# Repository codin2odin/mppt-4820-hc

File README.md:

# MPPT charge controller with HS load switch and CAN

 Development ongoing.

Schematic: [PDF file](build/mppt-4820-hc_schematic.pdf)

Bill of Materials: [CSV file](build/mppt-4820-hc_bom(hv_supply,can).csv)

Firmware repository: [charge-controller-firmware](https://github.com/codin2odin/charge-controller-firmware)

This charge controller design is modified version of [mppt-2420-hc](https://github.com/LibreSolar/mppt-2420-hc) with goal of adding support for 36v & 48v battery systems.

## Features

- Solar input terminal
    - Max. 85V (100V MOSFETs used)
    - DC/DC converter inductor current max. 20A
- Battery output terminal
    - 10 V - 60 V (supporting 12v & 24v & 36v & 48v battery systems)
    - Max. current: 20A (limited by inductor current)
- Load terminal: 20A
- New STM32G431 ARM MCU with advanced digital power conversion features
- Expandable via Olimex Universal Extension Connector (UEXT)
- Two bi-color (red/green) LEDs for status indication. Additional user interface can be included in separate PCB in front panel housing and connected via UEXT
- CAN interface via RJ45 connectors

## Mechanical design

- TO-220 MOSFETs can be screwed to large heat sink at the back

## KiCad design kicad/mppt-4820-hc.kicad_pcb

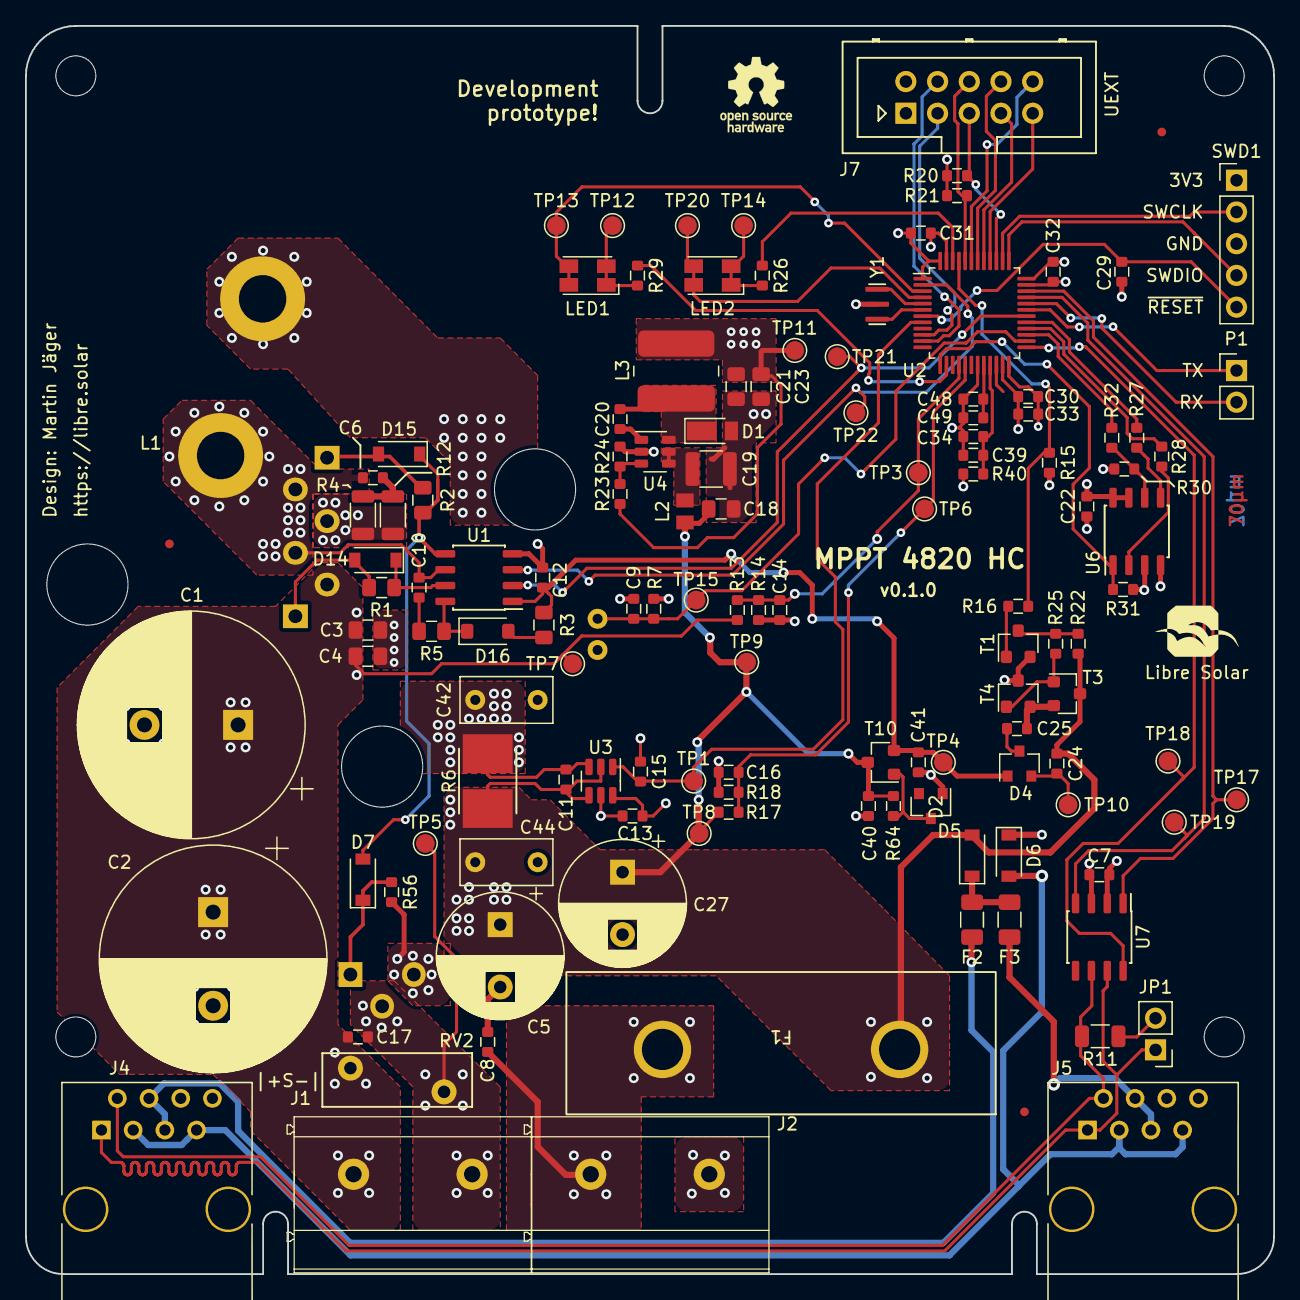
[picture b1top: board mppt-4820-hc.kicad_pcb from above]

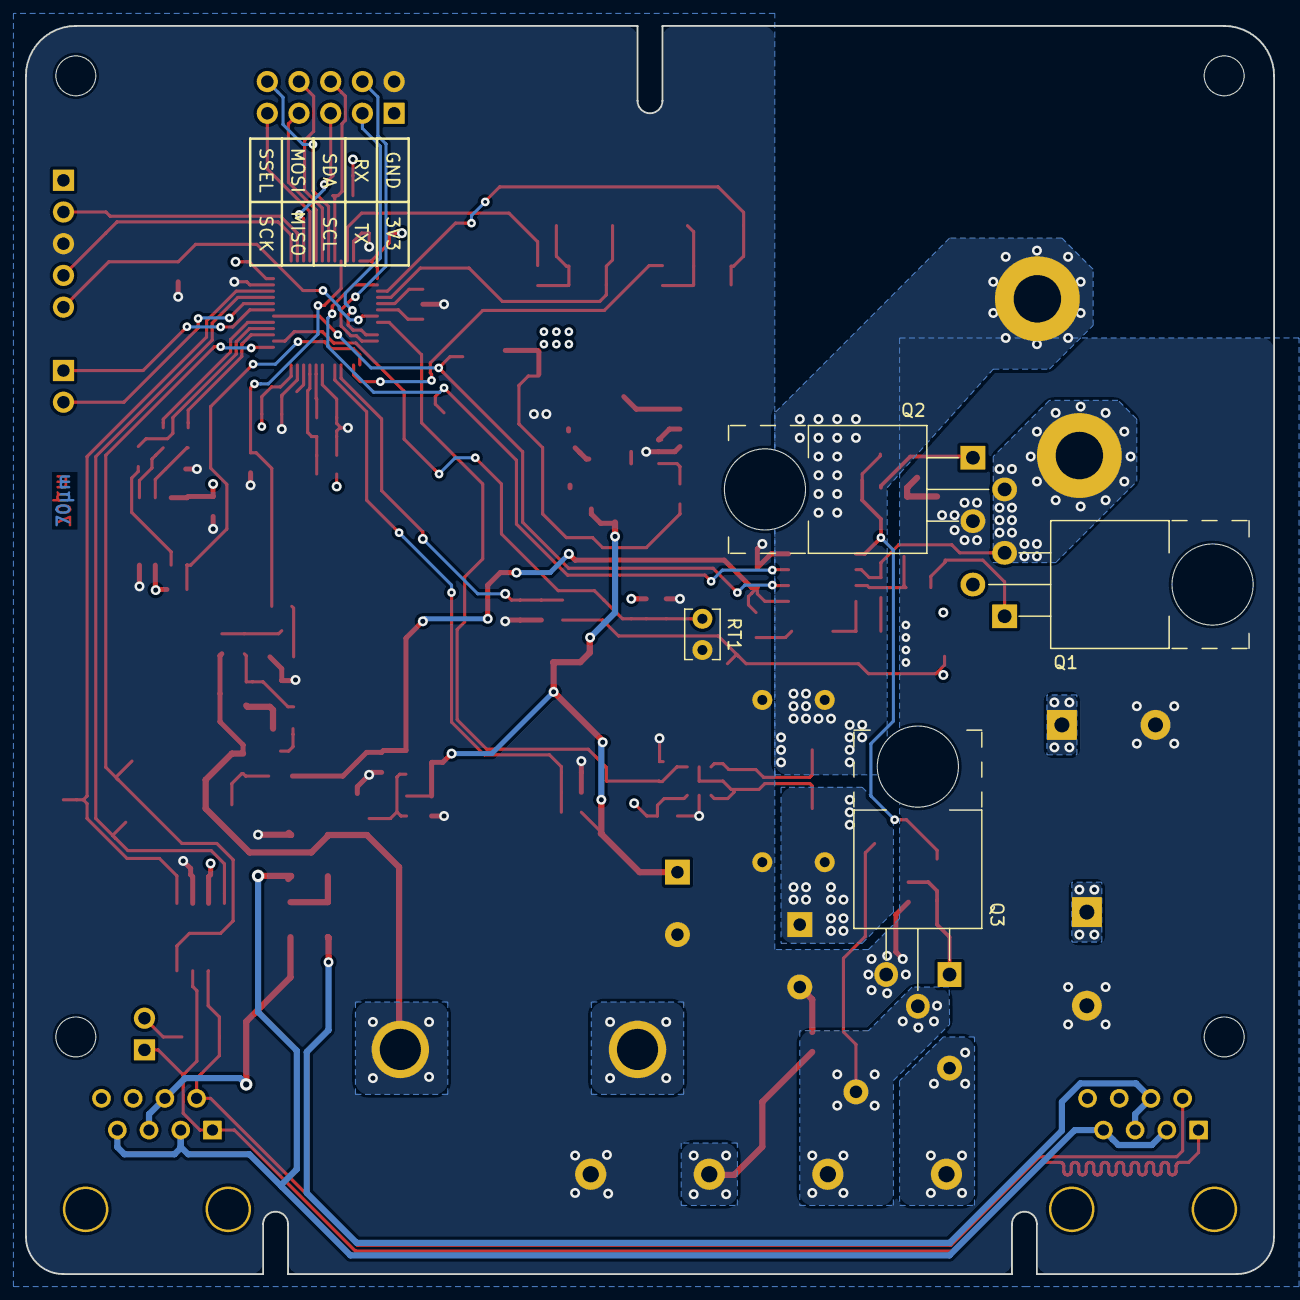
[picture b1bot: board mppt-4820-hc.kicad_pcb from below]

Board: 4 copper layers, 100.0 x 100.0 mm, 140 parts (4 on the bottom side), 76 nets.

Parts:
C1, C2: 560µF; CP_Radial_D18.0mm_P7.50mm
C3, C18: 1µF; C_0805_2012
C4: 100nF; C_0805_2012
C5, C27: 680µF; CP_Radial_D10.0mm_P5.00mm
C6: 2.2nF; C_0603_1608
C7, C9, C10, C13, C20, C22, C24, C29, C30, C31, C32, C48: 100nF; C_0603_1608
C8, C14, C16, C17, C25, C34: 10nF; C_0603_1608
C11, C15: 1nF; C_0603_1608
C12, C33, C39, C49: 2.2µF; C_0603_1608
C19: 4.7µF; C_1210_3225
C21, C23: 10µF; C_0805_2012
C40: 1µF; C_0603_1608
C41: 4.7µF; C_0603_1608
C42, C44: 0.22µF; C_Rect_L7.2mm_W3.5mm_P5.00mm_FKS2_FKP2_MKS2_MKP2
D1: SS16FP; D_PowerDI-123
D2, D6: NRVTS260ESFT1G; D_SOD-123
D4: BAS70-04; SOT-23
D5: 12V; D_SOT-23_ANK
D7, D14, D15: SS14FL; D_SOD-123
D16: 1N4148; D_SOD-123
F1: 25A; Eaton_S-4000
F2, F3: 500mA; Fuse_1206_3216Metric
FID1, FID2, FID3: Fiducial; Fiducial_0.7mm
J1, J2: MKDS 5/ 2-9,5; Phoenix_Contact_MKDS_5-2-9,5
J4, J5: 8P8C; RJ45_8P8C
J7: UEXT; Box_Header_2x05x2.54mm_Straight
JP1: Jumper_NC_Small; PinHeader_1x02_P2.54mm_Vertical
L1: 53µH; Inductor_Toroid_D32.8mm_4mm2
L2: 4.7µH; L_0805_2012Metric
L3: 47µH; Bourns_SRN6045TA
LED1, LED2: LED_Dual_PLCC4; LED_Avago_PLCC4_3.2x2.8mm_CW
LOGO1: LIBRE_SOLAR; LIBRESOLAR_LOGO
LOGO2: OPEN_HARDWARE; OSHW-Logo_5.7x6mm_SilkScreen
MK1, MK2, MK3, MK4: Mounting_Hole; MountingHole_3.2mm_M3
P1: CONN_01X02; PinHeader_1x02_P2.54mm_Vertical
Q1, Q2, Q3: IPA045N10N3G; TO-220-3_Horizontal_BottomHeatsink
R1, R2, R3, R5: 3R3; R_0805_2012
R4, R12: 4R7; R_1206_3216
R6: 2m; R_Bourns_CRE2512
R7, R16, R24, R64: 10k; R_0603_1608
R11: 120R; R_1206_3216Metric
R13, R17, R22, R30: 100k; R_0603_1608
R14, R20, R21, R31: 2.2k; R_0603_1608
R15, R56: 1M; R_0603_1608
R18: 5.6k; R_0603_1608
R23: 33k; R_0603_1608
R25, R26, R29: 1k; R_0603_1608
R27, R28, R32, R40: 47R; R_0603_1608
RT1: 10k; C_Disc_D3.8mm_W2.6mm_P2.50mm
RV2: 82V; RV_Disc_D12mm_W4.3mm_P7.5mm
SWD1: ST_Nucleo_SWD; PinHeader_1x05_P2.54mm_Vertical
T1, T3, T10: BC846B; SOT-23
T4: BC856B; SOT-23
TP1, TP3, TP4, TP5, TP6, TP7, TP8, TP9, TP10, TP11, TP12, TP13, TP14, TP15, TP17, TP18, TP19, TP20, TP21, TP22: 1.5mm; TestPoint_Pad_D1.5mm
U1: LM5107; SOIC-8_3.9x4.9mm_Pitch1.27mm
U2: STM32G431CBTx; LQFP-48_7x7mm_P0.5mm
U3: MPQ8112; TSOT-23-6
U4: LMR16006X; SOT-23-6
U6: W25Q80DVS; SOIC-8_3.9x4.9mm_Pitch1.27mm
U7: TCAN334; SOIC-8_3.9x4.9mm_Pitch1.27mm
Y1: 8MHz; Resonator_Murata_CSTNE

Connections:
+3V3: C7.1, C13.1, C21.1, C22.1, C23.1, C30.1, C31.1, C32.1, C33.1, J7.1 (3V3), L3.2, R7.1, R20.2, R21.2, R23.1, R31.2, R40.2, SWD1.1 (VCC), TP11.1, U2.1 (VBAT), U2.24 (VDD), U2.36 (VDD), U2.48 (VDD), U3.6 (EN), U6.3 (IO2), U6.7 (IO3), U6.8 (VCC), U7.3 (VCC)
+12V: C12.1, C41.1, D4.1, R3.2, T10.2 (E), TP4.1, U1.1 (VDD)
/BAT+: C8.1, F1.2, J2.1
/CAN/CAN_PWR1: F2.1, J4.4, J4.5
/CAN/CAN_PWR2: F3.1, J5.4, J5.5
/CAN/CAN_RX: TP19.1, U2.33 (PA11), U7.4 (RXD)
/CAN/CAN_STB: TP18.1, U2.25 (PB11), U7.8 (STB)
/CAN/CAN_TX: TP17.1, U2.34 (PA12), U7.1 (TXD)
/CAN_GND: D6.2 (A), J4.3, J4.7, J5.3, J5.7
/CAN_H: J4.1, J5.1, JP1.1, U7.7 (CANH)
/CAN_L: J4.2, J5.2, R11.2, U7.6 (CANL)
/DC/DC/HS_DRV: D14.1 (K), R1.2, U1.7 (HO)
/DC/DC/I_DCDC: C15.1, TP1.1, U2.8 (PA0), U3.1 (OUT)
/DC/DC/LS_DRV: D7.2 (A), D15.1 (K), R2.2, U1.5 (LO)
/DC/DC/PWM_HS: TP21.1, U1.2 (HI), U2.30 (PA8)
/DC/DC/PWM_LS: TP22.1, U1.3 (LI), U2.2 (PC13)
/DC/DC/SHUNT_DCDC_P: C11.1, C42.1, L1.2, R6.2, U3.3 (+)
/DC/DC/SW_NODE: C6.1, C10.2, L1.1, Q1.3 (S), Q2.2 (D), U1.6 (HS)
/DC/DC/V_DCDC_H: C14.1, R13.2, R14.1, TP3.1, U2.16 (PB0)
/DC/DC/V_DCDC_L: C16.1, R17.2, R18.1, TP6.1, U2.17 (PB1)
/DCDC_HV+: C1.1, C2.1, C3.1, C4.1, C17.1, J1.1, Q1.2 (D), R13.1, RV2.1, TP7.1
/DCDC_HV-: C17.2, J1.2, Q3.2 (D), RV2.2, TP5.1
/MCU/ADC1_IN11: C9.1, R7.2, RT1.1, TP15.1, U2.26 (PB12)
/MCU/GPIOC_14: LED1.2 (K1), LED1.3 (A2), TP13.1, U2.3 (PC14-OSC32_IN)
/MCU/GPIOC_15: LED2.2 (K1), LED2.3 (A2), TP20.1, U2.4 (PC15-OSC32_OUT)
/MCU/I2C1_SCL: J7.5 (SCL), R20.1, U2.39 (PA15)
/MCU/I2C1_SDA: J7.6 (SDA), R21.1, U2.44 (PB7)
/MCU/OSC_IN: U2.5 (PF0-OSC_IN), Y1.3
/MCU/OSC_OUT: U2.6 (PF1-OSC_OUT), Y1.1
/MCU/SPI1_MISO: J7.7 (MISO), U2.41 (PB4)
/MCU/SPI1_MOSI: J7.8 (MOSI), U2.42 (PB5)
/MCU/SPI1_SCK: J7.9 (SCK), U2.40 (PB3)
/MCU/SPI1_SSEL: J7.10 (SSEL), U2.43 (PB6)
/MCU/SPI2_CS: R31.1, U2.13 (PA5), U6.1 (~CS)
/MCU/SPI2_MISO: R28.1, U2.28 (PB14)
/MCU/SPI2_MOSI: R27.1, U2.29 (PB15)
/MCU/SPI2_SCK: R32.2, U2.27 (PB13)
/MCU/SWCLK: SWD1.2 (SWCLK), U2.38 (PA14)
/MCU/SWDIO: SWD1.4 (SWDIO), U2.37 (PA13)
/MCU/TIM8_CH2: R15.2, R16.2, U2.45 (PB8-BOOT0)
/MCU/TIM16_CH1: R29.2, U2.14 (PA6)
/MCU/TIM17_CH1: R26.2, U2.46 (PB9)
/MCU/USART1_RX: P1.2, U2.32 (PA10)
/MCU/USART1_TX: P1.1, U2.31 (PA9)
/MCU/USART2_RX: J7.4 (RXD), U2.11 (PA3)
/MCU/USART2_TX: J7.3 (TXD), U2.10 (PA2)
/MCU/~RESET: C29.1, SWD1.5 (NRST), U2.7 (NRST)
/Power supply/CP_OUT: C24.1, D4.2, TP10.1
/Power supply/CP_SW: C25.2, T3.2 (E), T4.2 (E)
GND: C1.2, C2.2, C3.2, C4.2, C5.2, C7.2, C8.2, C9.2, C12.2, C13.2, C14.2, C15.2, C16.2, C18.2, C19.2, C21.2, C22.2, C23.2, C27.2, C29.2, C30.2, C31.2, C32.2, C33.2, C34.2, C39.2, C40.2, C41.2, C42.2, C44.1, C48.2, C49.2, D1.2 (A), D5.2 (A), D6.1 (K), J2.2, J7.2 (GND), Q2.3 (S), Q3.3 (S), R4.1, R12.1, R14.2, R15.1, R18.2, R24.2, R30.1, R56.2, RT1.2, SWD1.3 (GND), T1.2 (E), T4.3 (C), U1.4 (VSS), U2.19 (VSSA), U2.23 (VSS), U2.35 (VSS), U2.47 (VSS), U3.5 (GND), U4.2 (GND), U6.4 (GND), U7.2 (GND), Y1.2
unnamed: C6.2, R4.2, R12.2
unnamed: C10.1, R5.2
unnamed: C25.1, D4.3
unnamed: C20.2, D1.1 (K), L3.1, U4.6 (SW)
unnamed: D2.1 (K), F2.2, F3.2
unnamed: D5.1 (K), R64.1, T10.1 (B)
unnamed: D7.1 (K), Q3.1 (G), R56.1
unnamed: D14.2 (A), Q1.1 (G), R1.1
unnamed: D15.2 (A), Q2.1 (G), R2.1
unnamed: D16.2 (A), R3.1
unnamed: D16.1 (K), R5.1, U1.8 (HB)
unnamed: JP1.2, R11.1
unnamed: LED1.1 (A1), LED1.4 (K2), R29.1, TP12.1
unnamed: LED2.1 (A1), LED2.4 (K2), R26.1, TP14.1
unnamed: R16.1, T1.1 (B)
unnamed: R22.1, R25.1, T1.3 (C)
unnamed: R25.2, T3.1 (B), T4.1 (B)
unnamed: C20.1, U4.1 (CB)
unnamed: C19.1, L2.2, U4.4 (EN), U4.5 (Vin)
unnamed: R23.2, R24.1, U4.3 (FB)
unnamed: R30.2, R32.1, U6.6 (CLK)
unnamed: R27.2, U6.5 (DI(IO0))
unnamed: R28.2, U6.2 (DO(IO1))
VBUS: C5.1, C11.2, C18.1, C24.2, C27.1, C40.1, C44.2, D2.2 (A), F1.1, L2.1, R6.1, R17.1, R22.2, R64.2, T3.3 (C), T10.3 (C), TP8.1, TP9.1, U3.2 (-), U3.4 (V+)
VDDA: C34.1, C39.1, R40.1, U2.21 (VDDA)
VREF: C48.1, C49.1, U2.20 (VREF+)

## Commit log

2023-01-07 initial 48v LV side kicad update:
    migrated files to KiCad 6
    replaced LV side current amp ic (60v)
    replaced caps in LV (63v)
    removed HV rail supply option
2023-01-07 bom & schematic files updates
2023-01-08 updated firmware link in readme
2023-01-08 updated inline 6.3x32 fuse holder in bom
2023-01-14 removed load terminal & circuit
2023-01-14 kicad files cleanup
2023-01-14 major changes
    removed Load terminal
    changed to 6.3x32mm fuse pcb holder
    added LibreSolar kicad footprint library locally
2023-01-18 minor component name fix
2023-02-15 pcb minor fixes, updated bom files, updated project name
2023-05-04 minor fixes & cleanup
2023-07-14 updated project to kicad 7
2023-07-18 some DRC check errors fixes (prototype 1)

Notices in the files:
kicad/mppt-4820-hc.kicad_pcb:
Licensed under CERN-OHL-W version 2
